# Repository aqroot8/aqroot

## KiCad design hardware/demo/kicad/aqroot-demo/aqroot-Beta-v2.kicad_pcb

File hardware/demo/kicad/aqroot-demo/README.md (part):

# AQROOT Full Beta v2 KiCad Project

This directory contains the KiCad 10 project for the **AQROOT Full Beta v2** main board.
It was forked from `hardware/beta-dm/` at FBV2-S1 and is the active design. Beta-DM
remains the preserved fallback and manufacturing baseline (D-005) and is **read-only**.

> **Provenance is measured, not asserted.** `checks/fork_equivalence.py` re-derives which
> forked files are still bit-identical to Beta-DM, which are identical after normalising the
> embedded project name, and which FBV2-S1 deliberately changed. The pinned result is
> `reports/FBV2-S1-fork-equivalence.md`.

## Current design state (2026-08-23, after FBV2-S1-007)

* Digital pin architecture: LOCKED to Beta Pin Map v0.2.4
* Schematic capture: **`01_POWER_TREE`, `02_MCU_CORE`, `03_SPI_A_DISPLAY_SD`,
  `04_SPI_B_RADIOS_NFC`, `05_I2C_DEVICES`, `06_AUDIO` and `07_IR` carry the Full Beta v2
  architecture. Sheets 08-09 are inherited from Beta-DM, unmodified, and still carry the
  Beta-DM architecture**
* ERC: **RUN.** **2 errors and 43 warnings, 45 messages total**
  (`reports/FBV2-S1-007-erc.rpt`) against a Beta-DM baseline of 5 errors / 53 warnings.
  **Zero introduced by any migration task.** The remaining warnings are mostly root-sheet
  `isolated_pin_label` entries on cross-sheet signals whose far end is an unmigrated sheet.
  This is not "ERC clean" — see FBV2-S2.
  **Read the counts with the right flags:** every figure in this programme is
  `kicad-cli sch erc --severity-error --severity-warning`, matching the reports' own
  *"Report includes: Errors, Warnings"* header. Adding `--severity-all` also counts
  **Exclusions** and reports **104** on the same unmodified design. **The "66 warnings" and
  "ERC 68" figures quoted here and in FBV2-S1-004 / 004B / 004C were transcription errors,
  corrected in FBV2-S1-005; the stored reports say 46 messages / 2 errors / 44 warnings.
  The reported deltas were always right**
* PCB placement and routing: **NOT STARTED. DO NOT START.** `aqroot-Beta-v2.kicad_pcb` is
  still a bit-identical copy of the Beta-DM board and does not match this schematic
* Schematic freeze: BLOCKED pending the remaining sheet migrations, ERC closeout, the
  footprint audit, RF review, DFM review, and unresolved part selections

> **This document is a Beta-DM-era file that FBV2-S1 has corrected only where it made a
> false statement about Full Beta v2.** Sections below that describe Beta-DM blocks and are
> still accurate have been left alone. Where a section is superseded it says so in place.

### Status vocabulary — read this before quoting any status in this file

| Term | Meaning |
|---|---|
| **SPECIFIED** | The design is written out in Markdown (this README / the Decisions Log). **Nothing has been drawn.** |
| **CAPTURED** | The block actually exists in the `.kicad_sch` file: real symbols, real wires, real nets. |

**These two are never interchangeable.** A block can be fully SPECIFIED — every part, value,
net name and layout note settled — and still be a completely empty sheet in KiCad. Do not
report a SPECIFIED block as captured, drawn, complete, or done.

### Capture status by sheet (2026-08-23, measured from the `.kicad_sch` files)

| Sheet | Status | Notes |
|---|---|---|
| `01_POWER_TREE` | **CAPTURED — FBV2-S1 POWER-TREE IMPLEMENTATION** | 136 parts, all with footprints. Reverse protection (P2) + LTC4368-1, autonomous dead-cell recovery, ACC_3V3 / ACC_5V accessory power, NFC 3V3-FIT / 5V-DNP select, VBUS_PRESENT and fault telemetry, 19 test points. `R95` = 560 R and the OV divider = 3.65 M / 442 k (4.63 V) per D-104 / D-105 |
| `02_MCU_CORE` | **CAPTURED — FBV2-S1 MCU-CORE MIGRATION** | 14 parts. `GPIO38 = NATIVE_A`, `GPIO47 = NATIVE_B`, `GPIO46 = DISP_BL_CTL` with a 10 k strap pull-down + 0 R isolation link + strap pad, `GPIO43` withdrawn from the community port (UART0 TXD + `TP35`), `GPIO3` strap pull-down (**B-09 closed**), `GPIO45` pull-down placed **DNP**. See [`GPIO_LEDGER.md`](../../../../docs/full-beta-v2/architecture/GPIO_LEDGER.md) |
| `03_SPI_A_DISPLAY_SD` | **CAPTURED — FBV2-S1 DISPLAY / TOUCH / microSD MIGRATION** | 21 parts. New `ER-TFT035IPS-6_50P` symbol with the vendor pin table verbatim — **the inherited 2.8-inch table had the backlight anode/cathode reversed and SCL / D-CX swapped**. `LED_A1..A4` collapse to one `LED_A`; backlight `R69` **1.87 R**, `R70`-`R73` **4 x 33 R** (109 mA typ, 117.6 mA worst case vs a 120 mA panel max); `TOUCH_INT_N` added (panel pin 46); `R112` 0 R **DNP** isolates the display SDO from the shared SPI-A, with `TP36`; `SD_CARD_DETECT_TBD` becomes **`SD_CARD_DETECT_N`** with `R113` 100 k. `J1` stays on the **FH69-dedicated** land pattern (**B-47**) |
| `04_SPI_B_RADIOS_NFC` | **CAPTURED — FBV2-S1 RADIOS / NFC MIGRATION** | 40 parts, A2 sheet. RF architecture locked: 433 MHz internal Taoglas `FXP450.07.0100C` on the `U7` IPEX, 915 MHz external to a top-panel SMA bulkhead, **no board RF trace in either band**; both module stamp-hole pins explicit NC. NFC: **`VDD`/`VDD_TX` moved to `NFC_SUPPLY` (B-41 closed)**, `Y1` 27.12 MHz crystal, full differential matching + RX divider with every value `TUNE`, `TP37`/`TP38` on the antenna terminals, `AAT`/`CSI`/`CSO`/`EXT_LM`/`MCU_CLK` explicit NC. `SX1262_DIO1` published for sheet `08`. **Zero `*_TBD` nets remain.** NFC IC and antenna **LOCKED**: `ST25R3916-AQET` non-B; Taoglas **`FXC.46.52.0075X.B.dg`** (reverse ferrite, adhesive to the inner rear shell) off-board on `J7` JST `BM02B-ACHSS-GAN-ETF` — replaceable without soldering. **First-build matching set calculated** (FBV2-S1-004C): target ≈ 36 Ω differential, `Q` ≈ 25, EMC cut-off 20.1 MHz, RFI divider fixed from 4.4 V pk-pk to 1.03 V pk-pk. Every value is a CALCULATED FIRST-BUILD VALUE, not a final tuned value |
| `05_I2C_DEVICES` | **CAPTURED — FBV2-S1 I²C / IMU MIGRATION** | 11 parts. `U4` BMI270 re-derived line by line against `BST-BMI270-DS000-08` Rev 1.6 — **every inherited strap proved correct** (D-136). Address strap made reworkable: **`R118` 0 Ω FIT to GND = 0x68, `R119` 0 Ω DNP to `+3V3` = 0x69, fit one only** (D-140). Internal I²C pull-ups `R19`/`R20` **4.7 kΩ → 2.2 kΩ** — 4.7 kΩ gave `t_r` 338 ns against the 300 ns fast-mode limit at the measured ≈ 85 pF (D-139). `INT1` stays on native GPIO3 with a **proven** boot-safe window and a mandatory push-pull / active-high firmware contract (D-137); `INT2` stays DNC (D-138). IMU permanently powered, no load switch (D-141). **B-44 CLOSED**; land pattern verified against §8.3 (D-143). Address map: `docs/full-beta-v2/architecture/I2C_ADDRESS_REGISTRY.md` |
| `06_AUDIO` | **CAPTURED — FBV2-S1 AUDIO MIGRATION** | A3 sheet. **`U5` and `J6` arrived DNP — the speaker output path had never been built — and are now FITTED** (D-144). **`MK1` = PUI `DMM-4026-B-I2S-R`, replacing the obsolete ICS-43434: SEVEN pads, not six, so a new symbol and footprint were built from the manufacturer drawing** (D-145); `CONFIG`→GND mandatory; **no 1.8 V rail needed**; **`R120` 100 kΩ on `I2S_MIC_DIN` is a data-sheet requirement**. **Bus rate is set by the microphone: 48 kHz × 64 = 3.072 MHz, decimate to 16 kHz in firmware** — 16 kHz on the wire is out of spec (D-146). `U5` = **`MAX98357AETE+T`**, `GAIN_SLOT` → VDD = **6 dB** because 12 dB clipped the top 6.8 dB of digital range against the 3.3 V rail (D-147). `LS1` = **PUI `AS02008MR-LW152-R`**, Ø20 × 3 mm, 8 Ω, 500–4000 Hz, AWG #32 leads crimping straight into `J6` (D-148). EMI recovery `R121`/`R122` 0 Ω FITTED + `C81`/`C82` 1 nF DNP (D-150). `LS1` remains the one part with no footprint, by design (off-board speaker) |
| `07_IR` | **CAPTURED — FBV2-S1 INFRARED MIGRATION** | A3 sheet. **Eight parts arrived DNP — the whole subsystem — and are now FITTED** (D-153), the fourth consecutive sheet with a load-bearing inherited DNP. `D1` = **Vishay `TSAL6100`** (940 nm, `Ie` 170 mW/sr, ±10°); **TSAL6200 is a proven drop-in fallback — identical package, `VF` and `IFM`, so `R24` is unchanged** (D-154). **Peak 150 mA = 75 % of the `IFM` 200 mA REPETITIVE rating**; `IFSM` 1.5 A is a single-pulse ≤ 5 µs surge and is not a carrier rating; 300 mA rejected as out of spec (D-155). **Supply `+3V3`, not `SYS`** — 118–170 mA regulated against 64–166 mA on `SYS` (D-156). `R24` 18 Ω → **12 Ω** plus `R123` DNP parallel trim, **never below 10 Ω** (D-157). `C12` 4.7 µF → **22 µF 1210** — 4.7 µF gave 218 mV of carrier ripple (D-158). **`Q1` AO3400A pinout CONFIRMED 1 = G / 2 = S / 3 = D; the "needs the official AOS land pattern" blocker is CLOSED because AOS publishes none** (D-159). `U6` = **`TSOP38438`**, a pure MPN change, and the inherited `R21`/`C11` filter is **quantified at 41 dB at 38 kHz — ~90× margin against the Fig. 7 knee, and it is what makes sharing `+3V3` safe** (D-160). `TP39`/`TP40` added. **O-5 open: Vishay marks AGC4 "No" for Sony code** — receive-only, and the `TSOP38238` symbol is retained so reverting is a `lib_id` change | TSOP38238 RX + TSAL6200 low-side NMOS TX |
| `08_BUTTONS_EXPANDERS` | **CAPTURED — INHERITED, BETA-DM ARCHITECTURE** | U60/U61 TCA9535PWR, 7 buttons, safe-state pulls |
| `09_COMMUNITY_HEADER` | **CAPTURED — INHERITED, BETA-DM ARCHITECTURE** | the 20-pin Beta-DM port. **Superseded by the 2x12 Samtec `BCS-112-S-D-HE` port (D-093); not yet migrated** |

**CAPTURED here means the symbols, wires and nets exist in the file.** It does not mean the
sheet carries the Full Beta v2 architecture. Only `01_POWER_TREE`, `02_MCU_CORE`,
`03_SPI_A_DISPLAY_SD` and `04_SPI_B_RADIOS_NFC` do.

Board-level status:

| Item | Status |
|---|---|
| PCB (`aqroot-Beta-v2.kicad_pcb`) | **INHERITED, BIT-IDENTICAL TO BETA-DM** — it is the Beta-DM board and **does not match this schematic**. No v2 placement or routing has been performed |
| ERC | **RUN 2026-08-23** — `reports/FBV2-S1-005-erc.rpt`, **2 errors / 43 warnings (45 messages)**; **zero introduced** by any migration task, and FBV2-S1-004 removed two inherited errors. Counts are `--severity-error --severity-warning`; `--severity-all` also counts Exclusions and reports 104 |
| Footprints assigned | **300 of 301 components** (`LS1`, the off-board speaker, is the exception). Assigned is not verified — the per-footprint pad-overlap audit against vendor drawings is **FBV2-S2** and has not run |

> The old claim that this project was an empty PCB with seven footprints and a never-run ERC
> described the Beta project at 2026-07-31. It is retained nowhere: it was false for Beta-DM
> from the moment that board was routed, and it is false for Full Beta v2.

## Locked GPIO expanders (v0.2.4, 2026-07-27)

Both I2C GPIO expanders are Texas Instruments TCA9535PWR, replacing the MCP23017.

* U60 = TCA9535PWR, I2C 0x20 (internal: buttons + control), straps A2=GND A1=GND A0=GND
* U61 = TCA9535PWR, I2C 0x21 (community header), straps A2=GND A1=GND A0=+3V3
* Package = PW, TSSOP-24, 0.65 mm pitch
* Symbol = `Interface_Expansion:TCA9535PWR`
* Footprint = `Package_SO:TSSOP-24_4.4x7.8mm_P0.65mm` (NOT yet audited — see rules)
* One open-drain active-low `/INT` per device, both wired-OR onto `WAKE_INT_N` -> ESP32 GPIO21

TCA9535PWR is datasheet-trusted and receives its first hardware validation on Beta. The Alpha
bench test that passed was an MCP23017, a different part.

## Explicit unresolved parts

* ~~External community-header I2C isolator or bus switch — **UNSELECTED.**~~ **LOCKED
  2026-08-07: TI `TCA9517ADGKR`, DGK / VSSOP-8** (U16). PCA9515A is not selected.
* ~~ACC_PWR_EN accessory load switch — **UNSELECTED.**~~ **LOCKED 2026-08-07: TI
  `TPS22918DBVR`, DBV / SOT-23-6** (U15).
* **Battery reverse-polarity protection — topology PARKED, see below**

> Both former candidates are now firm part locks. Their **footprints remain UNVERIFIED** —
> locking the part is a separate gate from comparing KiCad copper against the manufacturer
> land pattern. See *Nontrivial footprint verification policy* in [[05 - Design Decisions Log]].

## 01_POWER_TREE — CAPTURED (FBV2-S1, 2026-08-23)

**Sheet status: CAPTURED AND ERC-CHECKED. NOT FABRICATION READY.** The section that used to
stand here said the sheet was "SPECIFIED, NOT DRAWN" and that its `.kicad_sch` was an empty
stub. That was true on 2026-07-31 and is false now.

What exists in the file:

* USB-C 5 V sink / USB 2.0 front end, BQ25185 charger and power path, TPS63020 main `+3V3`
  buck-boost, TPS61023 NFC 5 V PA boost, MAX17048 fuel gauge, physical TPS63020 EN hard-off
* **Battery reverse protection, P2** — `J4` -> `F1` 5 A -> `BAT_RAW` -> `Q2` (stage 1) ->
  `BAT_MID` -> `Q3` (stage 2) -> `BAT_SENSE` -> `R75` 15 mR -> `BAT_PROTECTED_P` -> `U11` BAT,
  controlled by `U18` LTC4368-1. `RETRY` grounded (latch-off); `UV` unused, 510 k to VIN per
  the datasheet; `OV` divider `R77`/`R78`
* **Autonomous dead-cell recovery** — `U19` TLV7032, ratiometric polarity bridge, handoff
  comparator, `Q6`/`Q7`/`Q8` series 3-input AND, `Q9` FAULT inverter, `Q5` recovery P-FET,
  `R95` limit, `D12` unidirectional. USB-powered and firmware-independent
* **Accessory power** — `+3V3` -> `U20` TPS22950-Q1 -> `ACC_3V3_SW`; `BQ25185_SYS` -> `U21`
  TPS61023 -> `U22` TPS22950-Q1 -> `ACC_5V_SW`; both `FLT` pins wire-ORed to `ACC_POWER_FAULT_N`
* **NFC no-respin source select** — `R106` 0R **FIT** from `+3V3`, `R107` 0R **DNP** from the
  boost, mutually exclusive by fit state
* **Telemetry** — `VBUS_PRESENT` divided to 2.97 V at VBUS 5.0 V, `LTC4368_FAULT_N`,
  `ACC_POWER_FAULT_N`, `BQ25185_STAT1/2`

What is **not** true of it:

* it is **not fabrication ready**;
* **no footprint on this sheet has been verified** against a vendor drawing (FBV2-S2);
* **no PCB placement or routing has been performed**, and the inherited `.kicad_pcb` does not
  contain any of this;
* several component values are marked *value-to-verify* in the FBV2-S1 audit;
* `NFC_SUPPLY` has **no consumer yet** — `U9` VDD/VDD_TX are still on `NFC_5V_PA_PENDING` on
  sheet `04`, which FBV2-S1-001 was not authorised to modify.

### Reverse-polarity placeholder — RETIRED

**Superseded.** This section required the battery-input protection block to remain a labelled
placeholder that must never be instantiated. **FBV2-S1 instantiated it**, under D-050 / D-052 /
D-064 / D-068, after the topology was locked by FBV2-PWR-001 and FBV2-PWR-002.

`BAT_CONNECTOR_P` and `BAT_PROTECTED_P` **remain distinct nets** — that part of the old rule
still holds, and is now enforced by real components between them rather than by a text box.

The parallel link across the FETs remains **forbidden**. The in-series removable link in
`BAT_PROTECTED_P` remains permitted.

## TPS61023 NFC 5V PA boost — BETA LOCKED, CAPTURE APPROVED (2026-07-31)

| | |
|---|---|
| Part | **TI TPS61023DRLR**, adjustable synchronous boost |
| Package | **DRL, 6-pin SOT563 / SOT-5X3, 1.2 × 1.6 mm** — **do NOT substitute a generic SOT-23 footprint** |
| Symbol / footprint | **Not selected** — verify exact symbol pinout, exact TI DRL footprint, pin-1 orientation, exposed-pad status, manufacturer land pattern |
| In / Out | `BQ25185_SYS` → `NFC_5V_PA_PENDING` |
| Enable | `NFC_5V_EN` from TCA9535 **U60 P02** (100k safe-state pull-down already in the architecture) |
| Load | **ST25R3916 `VDD_PA` ONLY** |

> **FB divider values are PENDING-FROM-DATASHEET.** Inspect the current TPS61023 datasheet and
> EVM schematic and record the exact FB resistor values, inductor and capacitor recommendations
> at capture time. **Do not invent values from memory** — that is why no numbers appear here.

| Ref | Value |
|---|---|
| `U?` | TPS61023DRLR |
| `L_NFC_BOOST` | ~1 µH, **shielded**, low DCR, current rating from the TI design calculation; MPN may stay provisional |
| `C_NFC_BOOST_IN` | input ceramic — value/voltage/dielectric **from TI** |
| `C_NFC_BOOST_OUT` | output ceramic, **or the exact TI-recommended count** |
| `R_NFC_FB_TOP` / `R_NFC_FB_BOT` | FB divider for ~5.0 V — **exact values from the TI 5V reference/EVM** |
| `TP_NFC_5V_EN`, `TP_NFC_5V_PA` | test points |

**Do not connect** ST25R3916 `VDD_IO` (stays on `+3V3`), general 5V accessories, USB VBUS, or any
unrelated load.

```
NFC 5V PA RAIL ONLY
ST25R3916 VDD_IO REMAINS +3V3
NOT A GENERAL-PURPOSE 5V RAIL
```

```
DEFAULT OFF
ENABLE ONLY DURING NFC FIELD OPERATION
```

```
PLACE INDUCTOR, INPUT CAPACITOR AND OUTPUT CAPACITOR
TIGHT TO TPS61023

MINIMIZE SW NODE COPPER AREA

KEEP FB TRACE AWAY FROM SW AND INDUCTOR

PROVIDE SHORT DIRECT GROUND RETURNS
```

**ERC:** VIN is `BQ25185_SYS`; output is only `NFC_5V_PA_PENDING`; `VDD_IO` remains `+3V3`; EN is
`NFC_5V_EN`; the safe-state pull-down exists and no conflicting pull-up was added; FB is not
floating; no support capacitor or inductor omitted; symbol and DRL footprint pin numbering match.

## MAX17048 fuel gauge — BETA LOCKED, CAPTURE APPROVED (2026-07-31)

| | |
|---|---|
| Part | **ADI MAX17048G+T10** — prefer the **G** package over the **X** WLP for Beta assembly/inspection |
| Package | 8-pin 2 × 2 mm TDFN / LFCSP-style |
| Symbol / footprint | **Not selected** — verify official pinout and package drawing, assign the **exact manufacturer land pattern**, include the **exposed pad** if required |
| I²C address | **0x36**, no address configuration |
| Sense resistor | none required |

| Ref | Net |
|---|---|
| `VDD` | **`BAT_PROTECTED_P`** |
| `CELL` | **`BAT_PROTECTED_P`** or the exact recommended system-side sense node |
| `SDA` / `SCL` | `I2C_SDA_INT` / `I2C_SCL_INT` — **no second pull-up pair**, the bus already has the locked 4.7k |
| `ALRT_N` | **test point, otherwise unused**; no-connect marker if the datasheet allows. **Do not connect to `WAKE_INT_N`.** No new GPIO. |
| `C_FG_VDD` | **value from the current datasheet** — X7R, appropriate rating |
| `TP_FG_CELL` | test point |

```
MAX17048 MUST REMAIN BEHIND FINAL REVERSE-POLARITY PROTECTION
DO NOT CONNECT TO RAW BATTERY CONNECTOR POSITIVE
```

```
MAX17048 I2C ADDRESS 0x36
NO ADDRESS CONFIGURATION
```

```
MAX17048 — NEVER BENCH VALIDATED ON AQROOT

BETA BRING-UP REQUIRED:
- I2C detection at 0x36
- cell-voltage accuracy
- SOC plausibility
- charge/discharge response
- hibernate entry/exit
- battery insertion/removal
- charger-connected behavior
- hard-off behavior
- no I2C backpower
- firmware temperature compensation
- low-battery threshold validation
```

> **Do not check the "only one capacitor" assumption off** until the official typical application
> is reviewed for CELL filtering, VDD bypass, alert-network components and exposed-pad grounding.
> **Power-domain item:** the gauge stays battery-powered while `+3V3` is off, but the I²C
> pull-ups are on `+3V3`. Verify from the datasheet that SDA/SCL cannot back-power the disabled
> rail. No level shifting unless primary documentation requires it.

## Physical hard-off switch → TPS63020 EN (2026-07-31)

```
VINA -> [SPST maintained slide switch] -> EN
                                          |
                                   R_EN_PULLDOWN = 100k
                                          |
                                         GND
```

Closed → EN high → TPS63020 on → `+3V3` active. Open → 100k pulls EN low → TPS63020 off →
`+3V3` inactive. **No switch position, including mid-travel, can short VINA to GND** — which is
why SPST-plus-pull-down was chosen over the SPDT common/VINA/GND arrangement.

**Do not connect the switch to** ESP32 GPIO, TCA9535 GPIO, a firmware latch, battery ground, or
the raw battery current path.

**Switch part:** MPN provisional until mechanical review, **but the footprint must correspond to
a real candidate**. SPST preferred; **maintained** positions; low-profile side/top actuator;
through-hole mounting tabs preferred for strength; side-wall accessible; clear OFF/ON. **Do not
assign a tiny signal-switch footprint without checking** actuator travel, body dimensions,
mounting tabs, PCB edge setback, enclosure cutout and hand-solder access.

```
SWITCH POSITION / ACTUATOR / ENCLOSURE CUTOUT
REQUIRE FIELD SLATE MECHANICAL REVIEW BEFORE ROUTING
```

```
PHYSICAL MAIN-RAIL HARD OFF

SWITCH OFF:
TPS63020 DISABLED
+3V3 SYSTEM RAIL OFF

UPSTREAM BATTERY CIRCUITS REMAIN POWERED:
BQ25185
MAX17048
REVERSE-PROTECTION CONTROLLER CANDIDATE

TOTAL BATTERY STANDBY IS NOT ZERO
```

**Never claim** complete battery isolation, shipping mode, zero battery current or zero standby
draw. Soft push-button power UX / load-switch / latch / shipping-mode architecture is a
**post-Kickstarter option, not part of Beta**.

## USB-C 5V sink + USB 2.0 front end — BETA LOCKED, CAPTURE APPROVED (2026-07-30)

**Cleared to be drawn in `01_POWER_TREE` now.** Beta-locked, **not production-hardened** —
subject to professional power/DFM/EMI review before fabrication.

**Role: USB Type-C SINK / UFP. 5V only. USB 2.0 full-speed. NO PD, NO source role, NO DRP, NO
VCONN, NO alternate modes.**

### Connector

| | |
|---|---|
| Family | **GCT USB4105**, 16-contact USB 2.0 Type-C, top-mount horizontal, SMD contacts, TH shell stakes |
| Candidate MPN | **GCT USB4105-GF-A-120** — *verify drawing, shell-stake length vs PCB thickness, symbol pin numbering, and that the footprint matches the drawing before locking* |
| Footprint | `Connector_USB:USB_C_Receptacle_GCT_USB4105-xx-A_16P_TopMnt_Horizontal` |
| Symbol | 16-pin USB 2.0 Type-C receptacle — **verify pin numbering; do not use a 24-pin SuperSpeed symbol** |

Pin mapping: VBUS = **A4, B9, A9, B4** · GND = **A1, A12, B1, B12** · D+ = **A6, B6** ·
D− = **A7, B7** · CC1 = **A5** · CC2 = **B5** · SBU1 = **A8 (NC)** · SBU2 = **B8 (NC)** ·
shield tabs → `USB_SHIELD`.

> **A 16-contact receptacle has no SuperSpeed TX/RX contacts — do not invent them.** Join all
> duplicate VBUS, GND, D+ and D− contacts. Mark **only** SBU1/SBU2 no-connect.

### Components and reference designators

| Ref | Value | Notes |
|---|---|---|
| `J?` | GCT USB4105-GF-A-120 | suffix pending |
| `R_CC1_RD` | **5.1k, 1%** | CC1 → GND |
| `R_CC2_RD` | **5.1k, 1%** | CC2 → GND — **independent; never shared, never combined, never firmware-connected** |
| `U?` | **USBLC6-2SC6** (SOT-23-6) | verify pinout against the **ST datasheet** |
| `R_USB_VBUS_LINK` | 0R | optional bring-up current-measurement / isolation link |
| `C_USB_VBUS` | **4.7 µF**, 10 V min, X7R | **deliberately 4.7 µF, not 10 µF** — keeps hot-plug inrush conservative. MPN deferred to pre-fab BOM validation |
| `R_USB_DN_SER` | **22R** | D− series, **at the MCU end** |
| `R_USB_DP_SER` | **22R** | D+ series, **at the MCU end** — equal value + matching footprint; 33R is an option after SI review, **never mixed across the pair** |
| `C_USB_DN_EMC` | 100 pF **DNP** | MCU-side node → GND |
| `C_USB_DP_EMC` | 100 pF **DNP** | MCU-side node → GND |
| `R_USB_SHIELD_LINK` | **0R, populated** | `USB_SHIELD` → GND (Beta default) |
| `R_USB_SHIELD_BLEED` | 1M, **DNP** | alternative — **do not populate both without review** |

Optional DNP shield→GND capacitor footprint **only if board space permits**; no mandatory value.

### Nets

`USB_VBUS_RAW` · `USB_VBUS_CHG` · `USB_D_N_CONN` · `USB_D_P_CONN` · `USB_D_N_MCU` ·
`USB_D_P_MCU` · `USB_SHIELD` · `GND`

```
VBUS pins -> USB_VBUS_RAW -> [R_USB_VBUS_LINK 0R] -> USB_VBUS_CHG -> BQ25185 VIN
                  |
                  +-- C_USB_VBUS 4.7uF
                  +-- USBLC6 VBUS pin  (BRANCH — clamp reference, NOT series)

D- (A7,B7) -> USB_D_N_CONN -> USBLC6 ch -> R_USB_DN_SER 22R -> USB_D_N_MCU -> GPIO19
D+ (A6,B6) -> USB_D_P_CONN -> USBLC6 ch -> R_USB_DP_SER 22R -> USB_D_P_MCU -> GPIO20
```

**GPIO19 = D−, GPIO20 = D+. Do not cross.** `C_USB_VBUS` does **not** replace the bq25185's own
VIN decoupling, which is captured with the charger's support network.

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
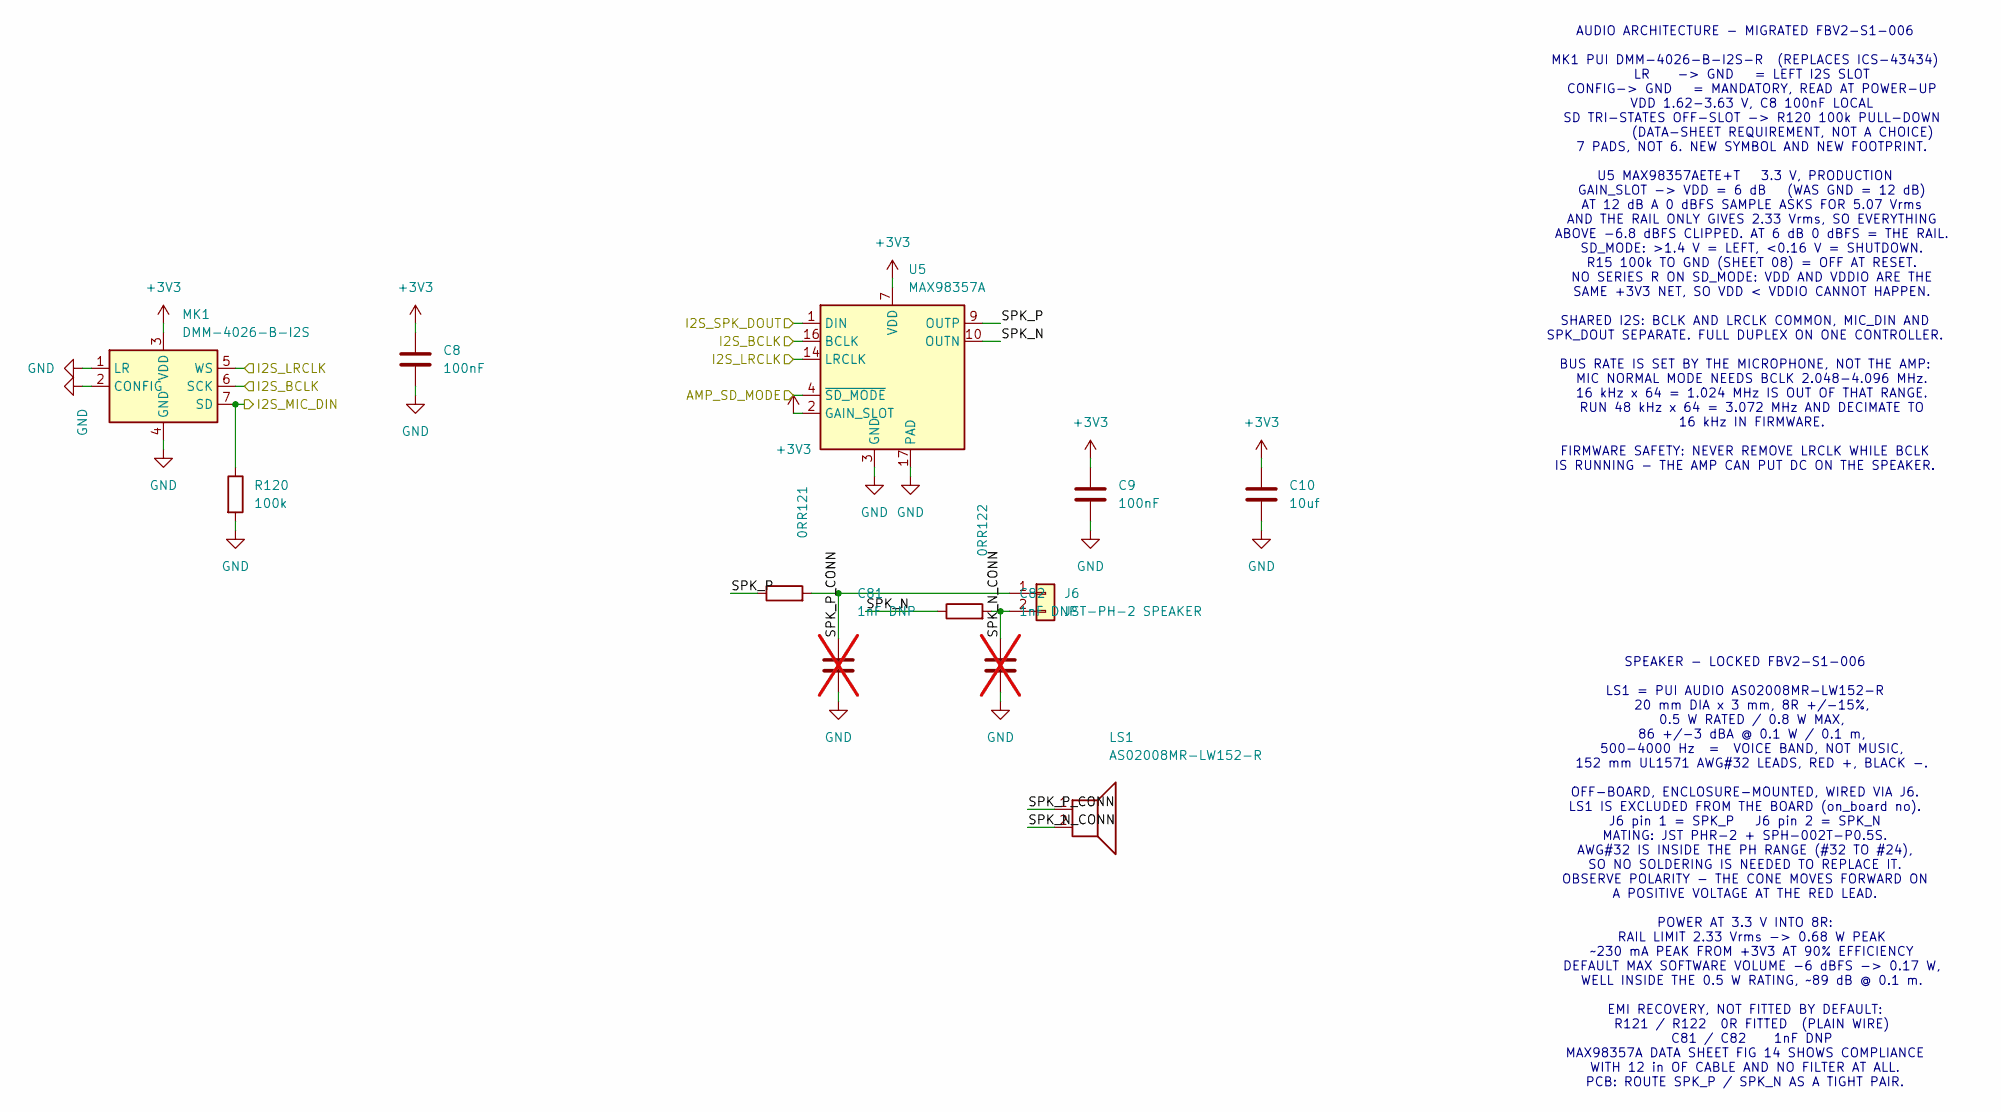
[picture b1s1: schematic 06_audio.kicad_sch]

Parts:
C8, C9: 100nF; C_0603_1608Metric; MPN CC0603KRX7R9BB104; LCSC C14663
C10: 10uf; C_0805_2012Metric; MPN GRM21BR61H106KE43L; LCSC C440198
C81, C82: 1nF DNP; C_0603_1608Metric; not fitted
J6: JST-PH-2 SPEAKER; JST_PH_B2B-PH-K_1x02_P2.00mm_Vertical; MPN B2B-PH-K-S(LF)(SN); LCSC C131337
LS1: AS02008MR-LW152-R; MPN AS02008MR-LW152-R; LCSC C3311653
MK1: DMM-4026-B-I2S; PUI_DMM-4026-B-I2S_4.0x3.0mm; MPN DMM-4026-B-I2S-R; LCSC C3171792
R120: 100k; R_0603_1608Metric; MPN 0603WAF1003T5E; LCSC C25803
R121, R122: 0R; R_0603_1608Metric; MPN 0603WAF0000T5E; LCSC C21189
U5: MAX98357A; TQFN-16-1EP_3x3mm_P0.5mm_EP1.23x1.23mm; MPN MAX98357AETE+T; LCSC C910544

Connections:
+3V3: C8.1, C9.1, C10.1, MK1.3 (VDD), U5.2 (GAIN_SLOT), U5.7 (VDD), U5.8 (VDD); also elsewhere on the board
/06_AUDIO/SPK_N: R122.1, U5.10 (OUTN)
/06_AUDIO/SPK_N_CONN: C82.1, J6.2, LS1.2, R122.2
/06_AUDIO/SPK_P: R121.1, U5.9 (OUTP)
/06_AUDIO/SPK_P_CONN: C81.1, J6.1, LS1.1, R121.2
/AMP_SD_MODE: U5.4 (~SD_MODE); also elsewhere on the board
/I2S_BCLK: MK1.6 (SCK), U5.16 (BCLK); also elsewhere on the board
/I2S_LRCLK: MK1.5 (WS), U5.14 (LRCLK); also elsewhere on the board
/I2S_MIC_DIN: MK1.7 (SD), R120.1; also elsewhere on the board
/I2S_SPK_DOUT: U5.1 (DIN); also elsewhere on the board
GND: C8.2, C9.2, C10.2, C81.2, C82.2, MK1.1 (LR), MK1.2 (CONFIG), MK1.4 (GND), R120.2, U5.3 (GND), U5.11 (GND), U5.15 (GND), U5.17 (PAD); also elsewhere on the board

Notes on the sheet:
AUDIO ARCHITECTURE - MIGRATED FBV2-S1-006 MK1 PUI DMM-4026-B-I2S-R (REPLACES ICS-43434) LR -> GND = LEFT I2S SLOT CONFIG-> GND = MANDATORY, READ AT POWER-UP VDD 1.62-3.63 V, C8 100nF LOCAL SD TRI-STATES OFF-SLOT -> R120 100k PULL-DOWN (DATA-SHEET REQUIREMENT, NOT A CHOICE) 7 PADS, NOT 6. NEW SYMBOL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
SPEAKER - LOCKED FBV2-S1-006 LS1 = PUI AUDIO AS02008MR-LW152-R 20 mm DIA x 3 mm, 8R +/-15%, 0.5 W RATED / 0.8 W MAX, 86 +/-3 dBA @ 0.1 W / 0.1 m, 500-4000 Hz = VOICE BAND, NOT MUSIC, 152 mm UL1571 AWG#32 LEADS, RED +, BLACK -. OFF-BOARD, ENCLOSURE-MOUNTED, WIRED VIA J6. LS1 IS EXCLUDED FROM THE BOA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

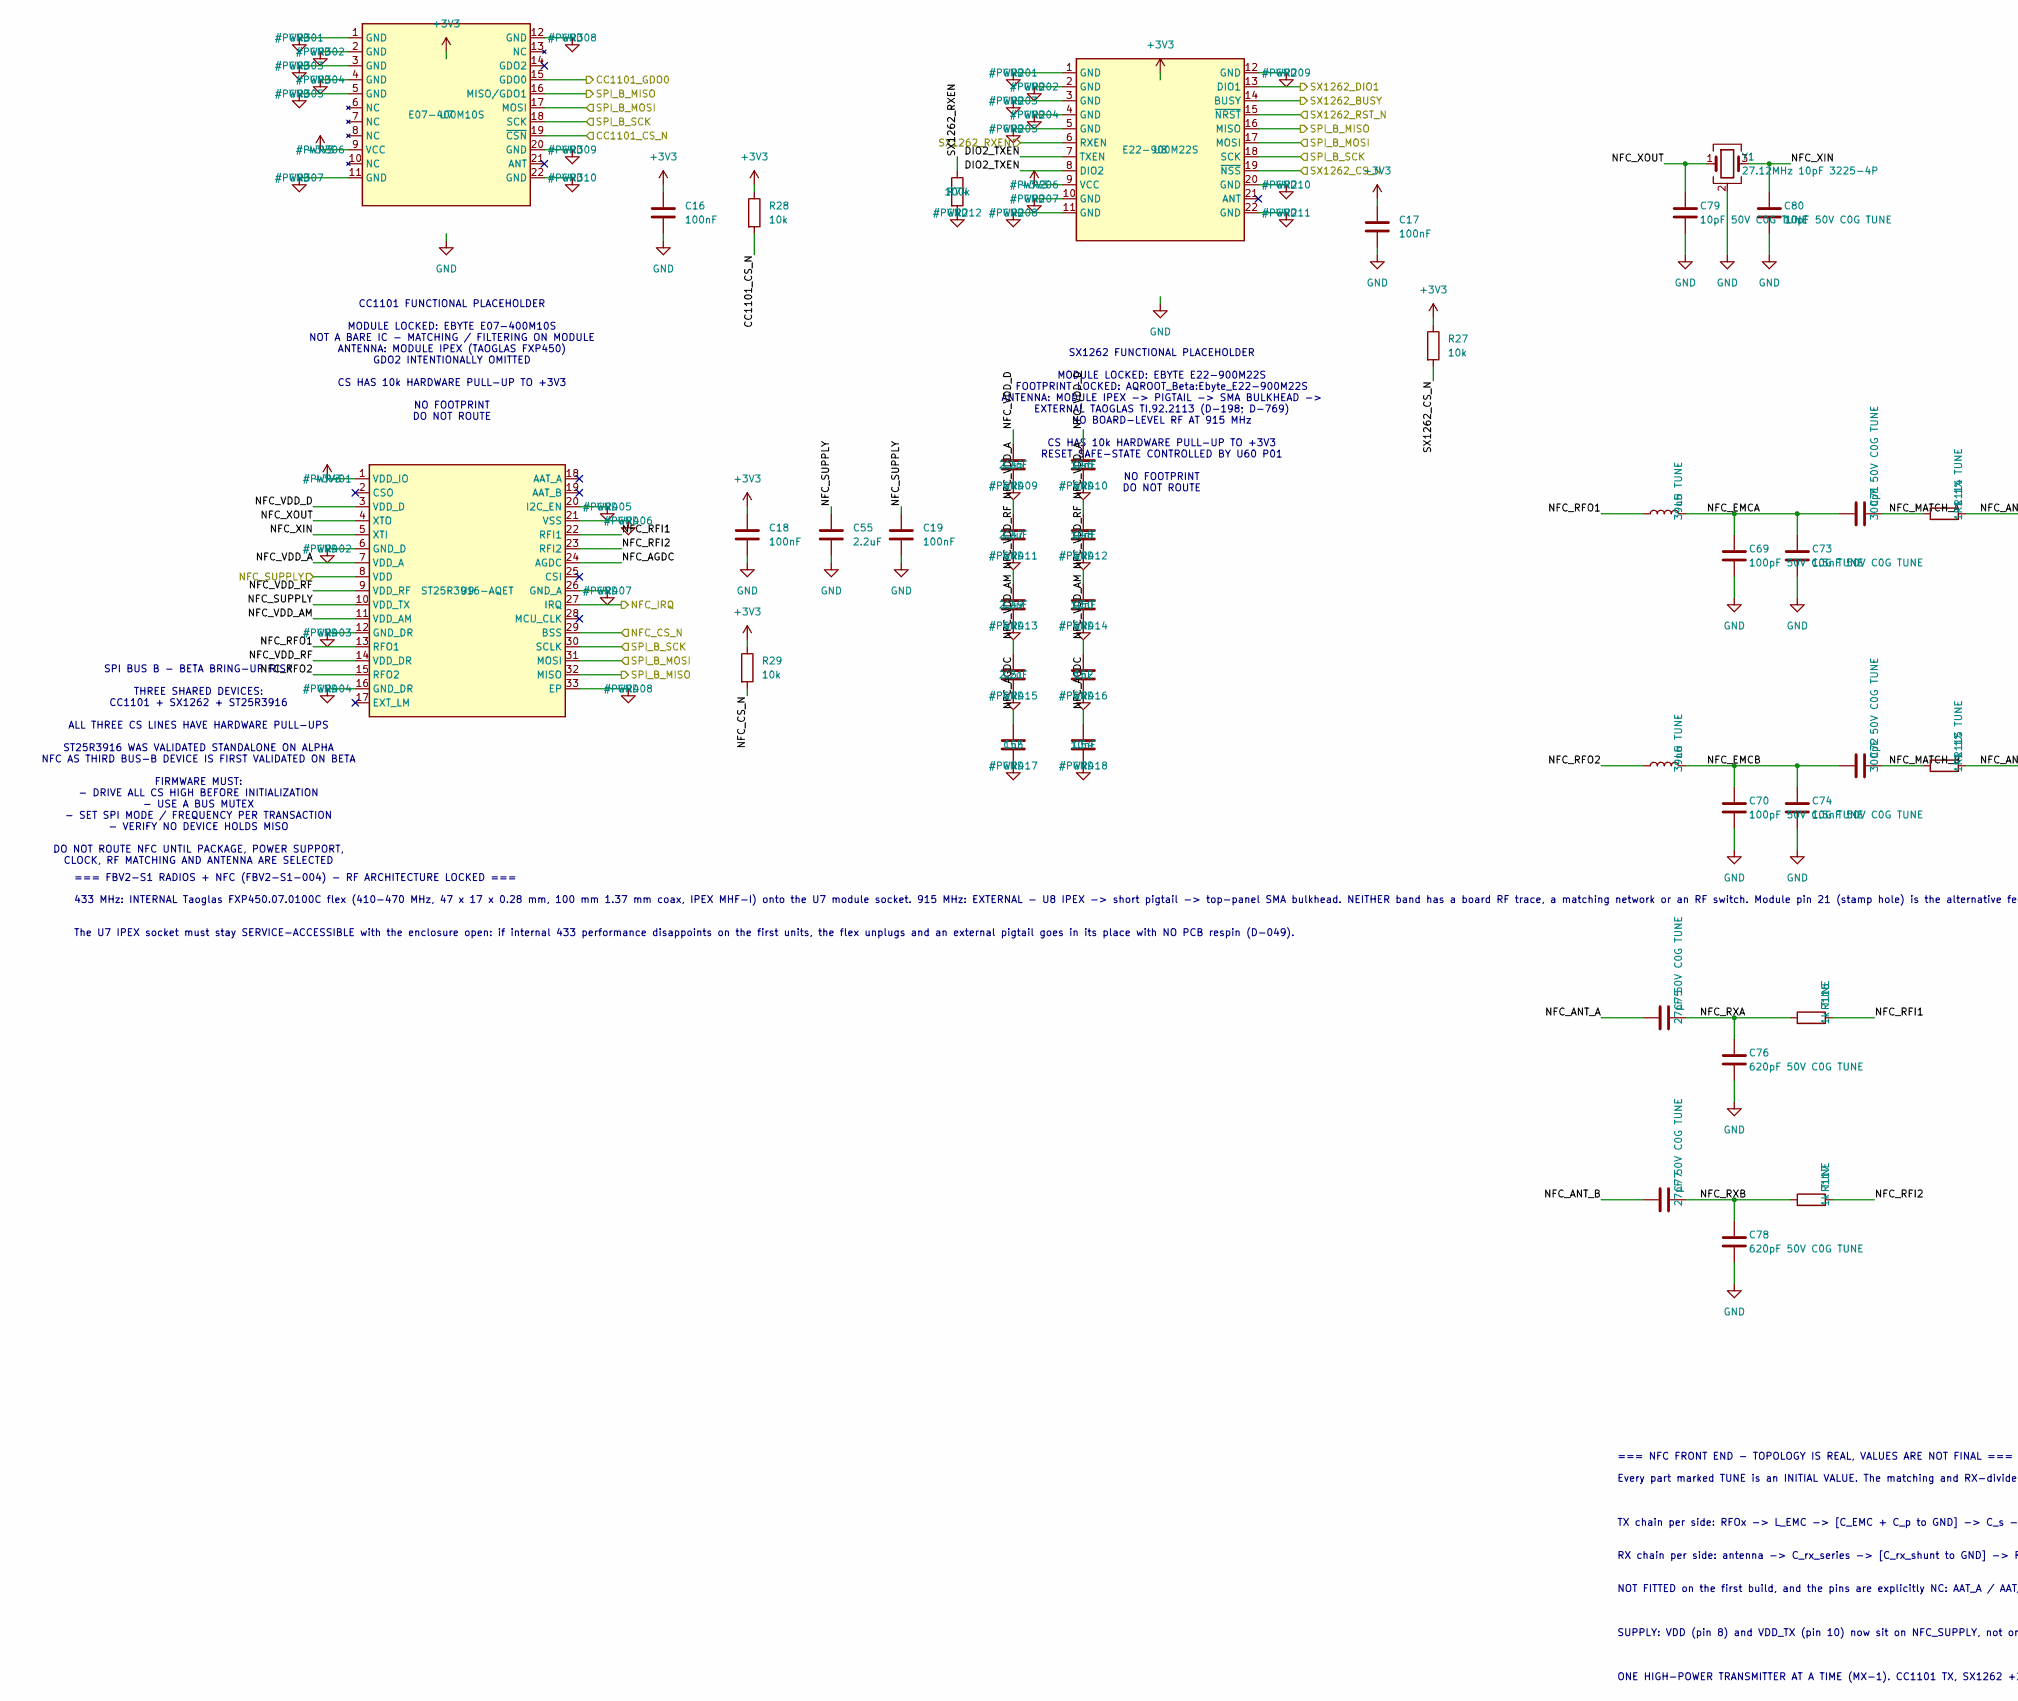
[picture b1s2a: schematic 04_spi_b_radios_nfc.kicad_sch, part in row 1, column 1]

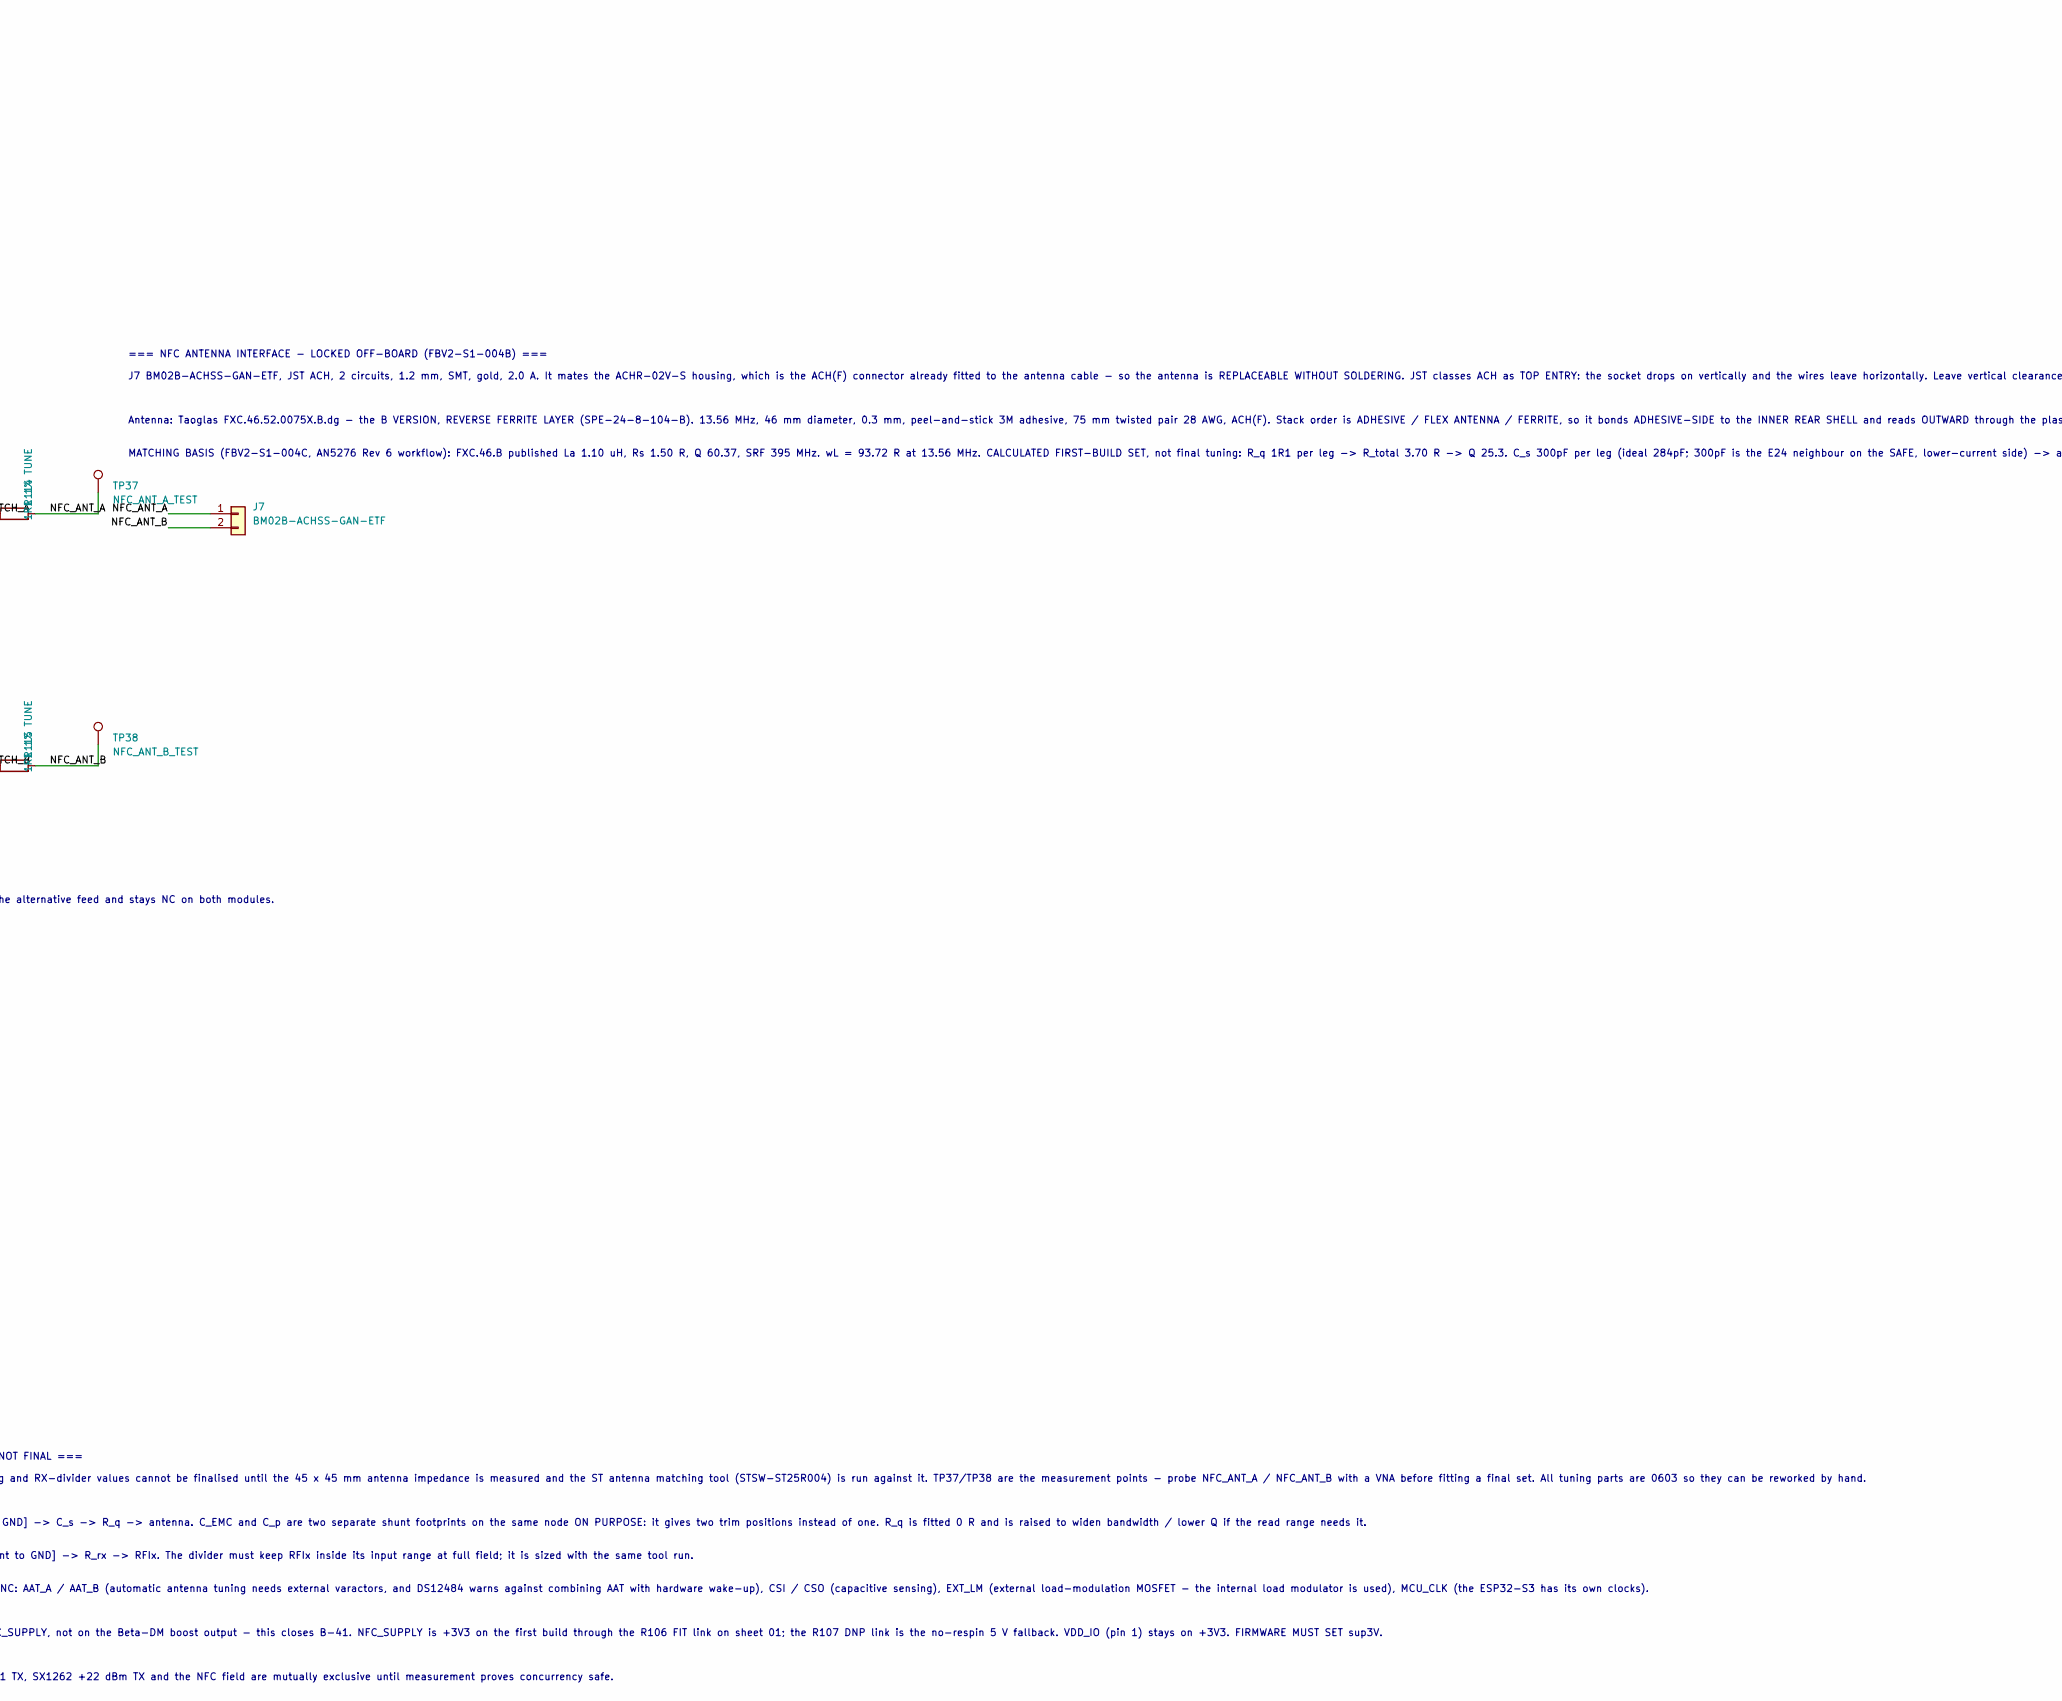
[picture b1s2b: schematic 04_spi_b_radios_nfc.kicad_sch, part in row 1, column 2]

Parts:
C16, C17: 100nF; C_0603_1608Metric; MPN CC0603KRX7R9BB104; LCSC C14663
C18, C19: 100nF; C_0402_1005Metric; Voltage 16V; MPN CC0402KRX7R8BB104; LCSC C105883
C45, C47, C49, C51: 2.2uF; C_0805_2012Metric; Voltage 16V; MPN CC0805KKX7R9BB225; LCSC C125847
C46, C48, C50, C54: 10nF; C_0603_1608Metric; Voltage 50V; MPN 0603B103K500NT; LCSC C57112
C52: 1nF; C_0603_1608Metric; Voltage 50V; MPN CL10B102KB8NNNC; LCSC C1588
C53: 1uF; C_0603_1608Metric; Voltage 16V; MPN CL10A105KB8NNNC; LCSC C15849
C55: 2.2uF; C_0603_1608Metric; Voltage 16V; MPN CL10A225KO8NNNC; LCSC C23630
C69, C70: 100pF 50V C0G TUNE; C_0603_1608Metric; MPN CL10C101JB8NNNC; LCSC C14858
C71, C72: 300pF 50V C0G TUNE; C_0603_1608Metric; MPN GCM1885C2A301FA16J; LCSC C3837533
C73, C74: 1.5nF 50V C0G TUNE; C_0603_1608Metric; MPN GCM1885C2A152JA16D; LCSC C388906
C75, C77: 27pF 50V C0G TUNE; C_0603_1608Metric; MPN GQM1875C2E270FB12D; LCSC C2360423
C76, C78: 620pF 50V C0G TUNE; C_0603_1608Metric; MPN CC0603JRNPO9BN621; LCSC C325470
C79, C80: 10pF 50V C0G TUNE; C_0603_1608Metric; MPN CL10C100JB8NNNC; LCSC C1634
J7: BM02B-ACHSS-GAN-ETF; JST_ACH_BM02B-ACHSS-GAN-ETF_1x02-1MP_P1.20mm_Vertical; MPN BM02B-ACHSS-GAN-ETF(LF)(SN); LCSC C5118738
L5, L6: 39nH TUNE; L_0603_1608Metric; MPN LQW18AN39NG80D; LCSC C2042966
R27, R28, R29: 10k; R_0603_1608Metric; MPN 0603WAF1002T5E; LCSC C25804
R74: 100k; R_0603_1608Metric; Tolerance 1%; MPN 0603WAF1003T5E; LCSC C25803
R114, R115: 1R1 1% TUNE; R_0603_1608Metric; MPN RC0603FR-071R1L; LCSC C309559
R116, R117: 1k TUNE; R_0603_1608Metric; MPN 0603WAF1001T5E; LCSC C21190
TP37: NFC_ANT_A_TEST; TestPoint_Pad_D1.0mm
TP38: NFC_ANT_B_TEST; TestPoint_Pad_D1.0mm
U7: E07-400M10S; Ebyte_E07-400M10S; MPN E07-400M10S; LCSC C2965513
U8: E22-900M22S; Ebyte_E22-900M22S; MPN E22-900M22S; LCSC C411293
U9: ST25R3916-AQET; ST25R3916_AQET; MPN ST25R3916-AQET; LCSC C5267441
Y1: 27.12MHz 10pF 3225-4P; Crystal_SMD_3225-4Pin_3.2x2.5mm; MPN TXM27.12M0004322DBBDO00T; LCSC C362365

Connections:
+3V3: C16.1, C17.1, C18.1, R27.1, R28.1, R29.1, U7.9 (VCC), U8.9 (VCC), U9.1 (VDD_IO); also elsewhere on the board
/04_SPI_B_RADIOS_NFC/DIO2_TXEN: U8.7 (TXEN), U8.8 (DIO2)
/04_SPI_B_RADIOS_NFC/NFC_AGDC: C53.1, C54.1, U9.24 (AGDC)
/04_SPI_B_RADIOS_NFC/NFC_ANT_A: C75.1, J7.1, R114.2, TP37.1
/04_SPI_B_RADIOS_NFC/NFC_ANT_B: C77.1, J7.2, R115.2, TP38.1
/04_SPI_B_RADIOS_NFC/NFC_EMCA: C69.1, C71.1, C73.1, L5.2
/04_SPI_B_RADIOS_NFC/NFC_EMCB: C70.1, C72.1, C74.1, L6.2
/04_SPI_B_RADIOS_NFC/NFC_MATCH_A: C71.2, R114.1
/04_SPI_B_RADIOS_NFC/NFC_MATCH_B: C72.2, R115.1
/04_SPI_B_RADIOS_NFC/NFC_RFI1: R116.2, U9.22 (RFI1)
/04_SPI_B_RADIOS_NFC/NFC_RFI2: R117.2, U9.23 (RFI2)
/04_SPI_B_RADIOS_NFC/NFC_RFO1: L5.1, U9.13 (RFO1)
/04_SPI_B_RADIOS_NFC/NFC_RFO2: L6.1, U9.15 (RFO2)
/04_SPI_B_RADIOS_NFC/NFC_RXA: C75.2, C76.1, R116.1
/04_SPI_B_RADIOS_NFC/NFC_RXB: C77.2, C78.1, R117.1
/04_SPI_B_RADIOS_NFC/NFC_VDD_A: C47.1, C48.1, U9.7 (VDD_A)
/04_SPI_B_RADIOS_NFC/NFC_VDD_AM: C51.1, C52.1, U9.11 (VDD_AM)
/04_SPI_B_RADIOS_NFC/NFC_VDD_D: C45.1, C46.1, U9.3 (VDD_D)
/04_SPI_B_RADIOS_NFC/NFC_VDD_RF: C49.1, C50.1, U9.9 (VDD_RF), U9.14 (VDD_DR)
/04_SPI_B_RADIOS_NFC/NFC_XIN: C80.1, U9.5 (XTI), Y1.3
/04_SPI_B_RADIOS_NFC/NFC_XOUT: C79.1, U9.4 (XTO), Y1.1
/CC1101_CS_N: R28.2, U7.19 (~CSN); also elsewhere on the board
/CC1101_GDO0: U7.15 (GDO0); also elsewhere on the board
/NFC_CS_N: R29.2, U9.29 (BSS); also elsewhere on the board
/NFC_IRQ: U9.27 (IRQ); also elsewhere on the board
/NFC_SUPPLY: C19.1, C55.1, U9.8 (VDD), U9.10 (VDD_TX); also elsewhere on the board
/SPI_B_MISO: U7.16 (MISO/GDO1), U8.16 (MISO), U9.32 (MISO); also elsewhere on the board
/SPI_B_MOSI: U7.17 (MOSI), U8.17 (MOSI), U9.31 (MOSI); also elsewhere on the board
/SPI_B_SCK: U7.18 (SCK), U8.18 (SCK), U9.30 (SCLK); also elsewhere on the board
/SX1262_BUSY: U8.14 (BUSY); also elsewhere on the board
/SX1262_CS_N: R27.2, U8.19 (~NSS); also elsewhere on the board
/SX1262_DIO1: U8.13 (DIO1); also elsewhere on the board
/SX1262_RST_N: U8.15 (~NRST); also elsewhere on the board
/SX1262_RXEN: R74.1, U8.6 (RXEN); also elsewhere on the board
GND: C16.2, C17.2, C18.2, C19.2, C45.2, C46.2, C47.2, C48.2, C49.2, C50.2, C51.2, C52.2, C53.2, C54.2, C55.2, C69.2, C70.2, C73.2, C74.2, C76.2, C78.2, C79.2, C80.2, R74.2, U7.1 (GND), U7.2 (GND), U7.3 (GND), U7.4 (GND), U7.5 (GND), U7.11 (GND), U7.12 (GND), U7.20 (GND), U7.22 (GND), U8.1 (GND), U8.2 (GND), U8.3 (GND), U8.4 (GND), U8.5 (GND), U8.10 (GND), U8.11 (GND), U8.12 (GND), U8.20 (GND), U8.22 (GND), U9.6 (GND_D), U9.12 (GND_DR), U9.16 (GND_DR), U9.20 (I2C_EN), U9.21 (VSS), U9.26 (GND_A), U9.33 (EP), Y1.2 (G), Y1.4 (G); also elsewhere on the board

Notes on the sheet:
CC1101 FUNCTIONAL PLACEHOLDER MODULE LOCKED: EBYTE E07-400M10S NOT A BARE IC - MATCHING / FILTERING ON MODULE ANTENNA: MODULE IPEX (TAOGLAS FXP450) GDO2 INTENTIONALLY OMITTED CS HAS 10k HARDWARE PULL-UP TO +3V3 NO FOOTPRINT DO NOT ROUTE
SPI BUS B - BETA BRING-UP RISK THREE SHARED DEVICES: CC1101 + SX1262 + ST25R3916 ALL THREE CS LINES HAVE HARDWARE PULL-UPS ST25R3916 WAS VALIDATED STANDALONE ON ALPHA NFC AS THIRD BUS-B DEVICE IS FIRST VALIDATED ON BETA FIRMWARE MUST: - DRIVE ALL CS HIGH BEFORE INITIALIZATION - USE A BUS MUTEX - SE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
SX1262 FUNCTIONAL PLACEHOLDER MODULE LOCKED: EBYTE E22-900M22S FOOTPRINT LOCKED: AQROOT_Beta:Ebyte_E22-900M22S ANTENNA: MODULE IPEX -> PIGTAIL -> SMA BULKHEAD -> EXTERNAL TAOGLAS TI.92.2113 (D-198; D-769) NO BOARD-LEVEL RF AT 915 MHz CS HAS 10k HARDWARE PULL-UP TO +3V3 RESET SAFE-STATE CONTROLLED B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
=== FBV2-S1 RADIOS + NFC (FBV2-S1-004) - RF ARCHITECTURE LOCKED ===
433 MHz: INTERNAL Taoglas FXP450.07.0100C flex (410-470 MHz, 47 x 17 x 0.28 mm, 100 mm 1.37 mm coax, IPEX MHF-I) onto the U7 module socket. 915 MHz: EXTERNAL - U8 IPEX -> short pigtail -> top-panel SMA bulkhead. NEITHER band has a board RF trace, a matching network or an RF switch. Module pin 21 (s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
The U7 IPEX socket must stay SERVICE-ACCESSIBLE with the enclosure open: if internal 433 performance disappoints on the first units, the flex unplugs and an external pigtail goes in its place with NO PCB respin (D-049).
=== NFC FRONT END - TOPOLOGY IS REAL, VALUES ARE NOT FINAL ===
Every part marked TUNE is an INITIAL VALUE. The matching and RX-divider values cannot be finalised until the 45 x 45 mm antenna impedance is measured and the ST antenna matching tool (STSW-ST25R004) is run against it. TP37/TP38 are the measurement points - probe NFC_ANT_A / NFC_ANT_B with a VNA bef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
TX chain per side: RFOx -> L_EMC -> [C_EMC + C_p to GND] -> C_s -> R_q -> antenna. C_EMC and C_p are two separate shunt footprints on the same node ON PURPOSE: it gives two trim positions instead of one. R_q is fitted 0 R and is raised to widen bandwidth / lower Q if the read range needs it.
RX chain per side: antenna -> C_rx_series -> [C_rx_shunt to GND] -> R_rx -> RFIx. The divider must keep RFIx inside its input range at full field; it is sized with the same tool run.
NOT FITTED on the first build, and the pins are explicitly NC: AAT_A / AAT_B (automatic antenna tuning needs external varactors, and DS12484 warns against combining AAT with hardware wake-up), CSI / CSO (capacitive sensing), EXT_LM (external load-modulation MOSFET - the internal load modulator is u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
SUPPLY: VDD (pin 8) and VDD_TX (pin 10) now sit on NFC_SUPPLY, not on the Beta-DM boost output - this closes B-41. NFC_SUPPLY is +3V3 on the first build through the R106 FIT link on sheet 01; the R107 DNP link is the no-respin 5 V fallback. VDD_IO (pin 1) stays on +3V3. FIRMWARE MUST SET sup3V.
ONE HIGH-POWER TRANSMITTER AT A TIME (MX-1). CC1101 TX, SX1262 +22 dBm TX and the NFC field are mutually exclusive until measurement proves concurrency safe.
=== NFC ANTENNA INTERFACE - LOCKED OFF-BOARD (FBV2-S1-004B) ===
J7 BM02B-ACHSS-GAN-ETF, JST ACH, 2 circuits, 1.2 mm, SMT, gold, 2.0 A. It mates the ACHR-02V-S housing, which is the ACH(F) connector already fitted to the antenna cable - so the antenna is REPLACEABLE WITHOUT SOLDERING. JST classes ACH as TOP ENTRY: the socket drops on vertically and the wires lea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
Antenna: Taoglas FXC.46.52.0075X.B.dg - the B VERSION, REVERSE FERRITE LAYER (SPE-24-8-104-B). 13.56 MHz, 46 mm diameter, 0.3 mm, peel-and-stick 3M adhesive, 75 mm twisted pair 28 AWG, ACH(F). Stack order is ADHESIVE / FLEX ANTENNA / FERRITE, so it bonds ADHESIVE-SIDE to the INNER REAR SHELL and re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
MATCHING BASIS (FBV2-S1-004C, AN5276 Rev 6 workflow): FXC.46.B published La 1.10 uH, Rs 1.50 R, Q 60.37, SRF 395 MHz. wL = 93.72 R at 13.56 MHz. CALCULATED FIRST-BUILD SET, not final tuning: R_q 1R1 per leg -> R_total 3.70 R -> Q 25.3. C_s 300pF per leg (ideal 284pF; 300pF is the E24 neighbour on t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
